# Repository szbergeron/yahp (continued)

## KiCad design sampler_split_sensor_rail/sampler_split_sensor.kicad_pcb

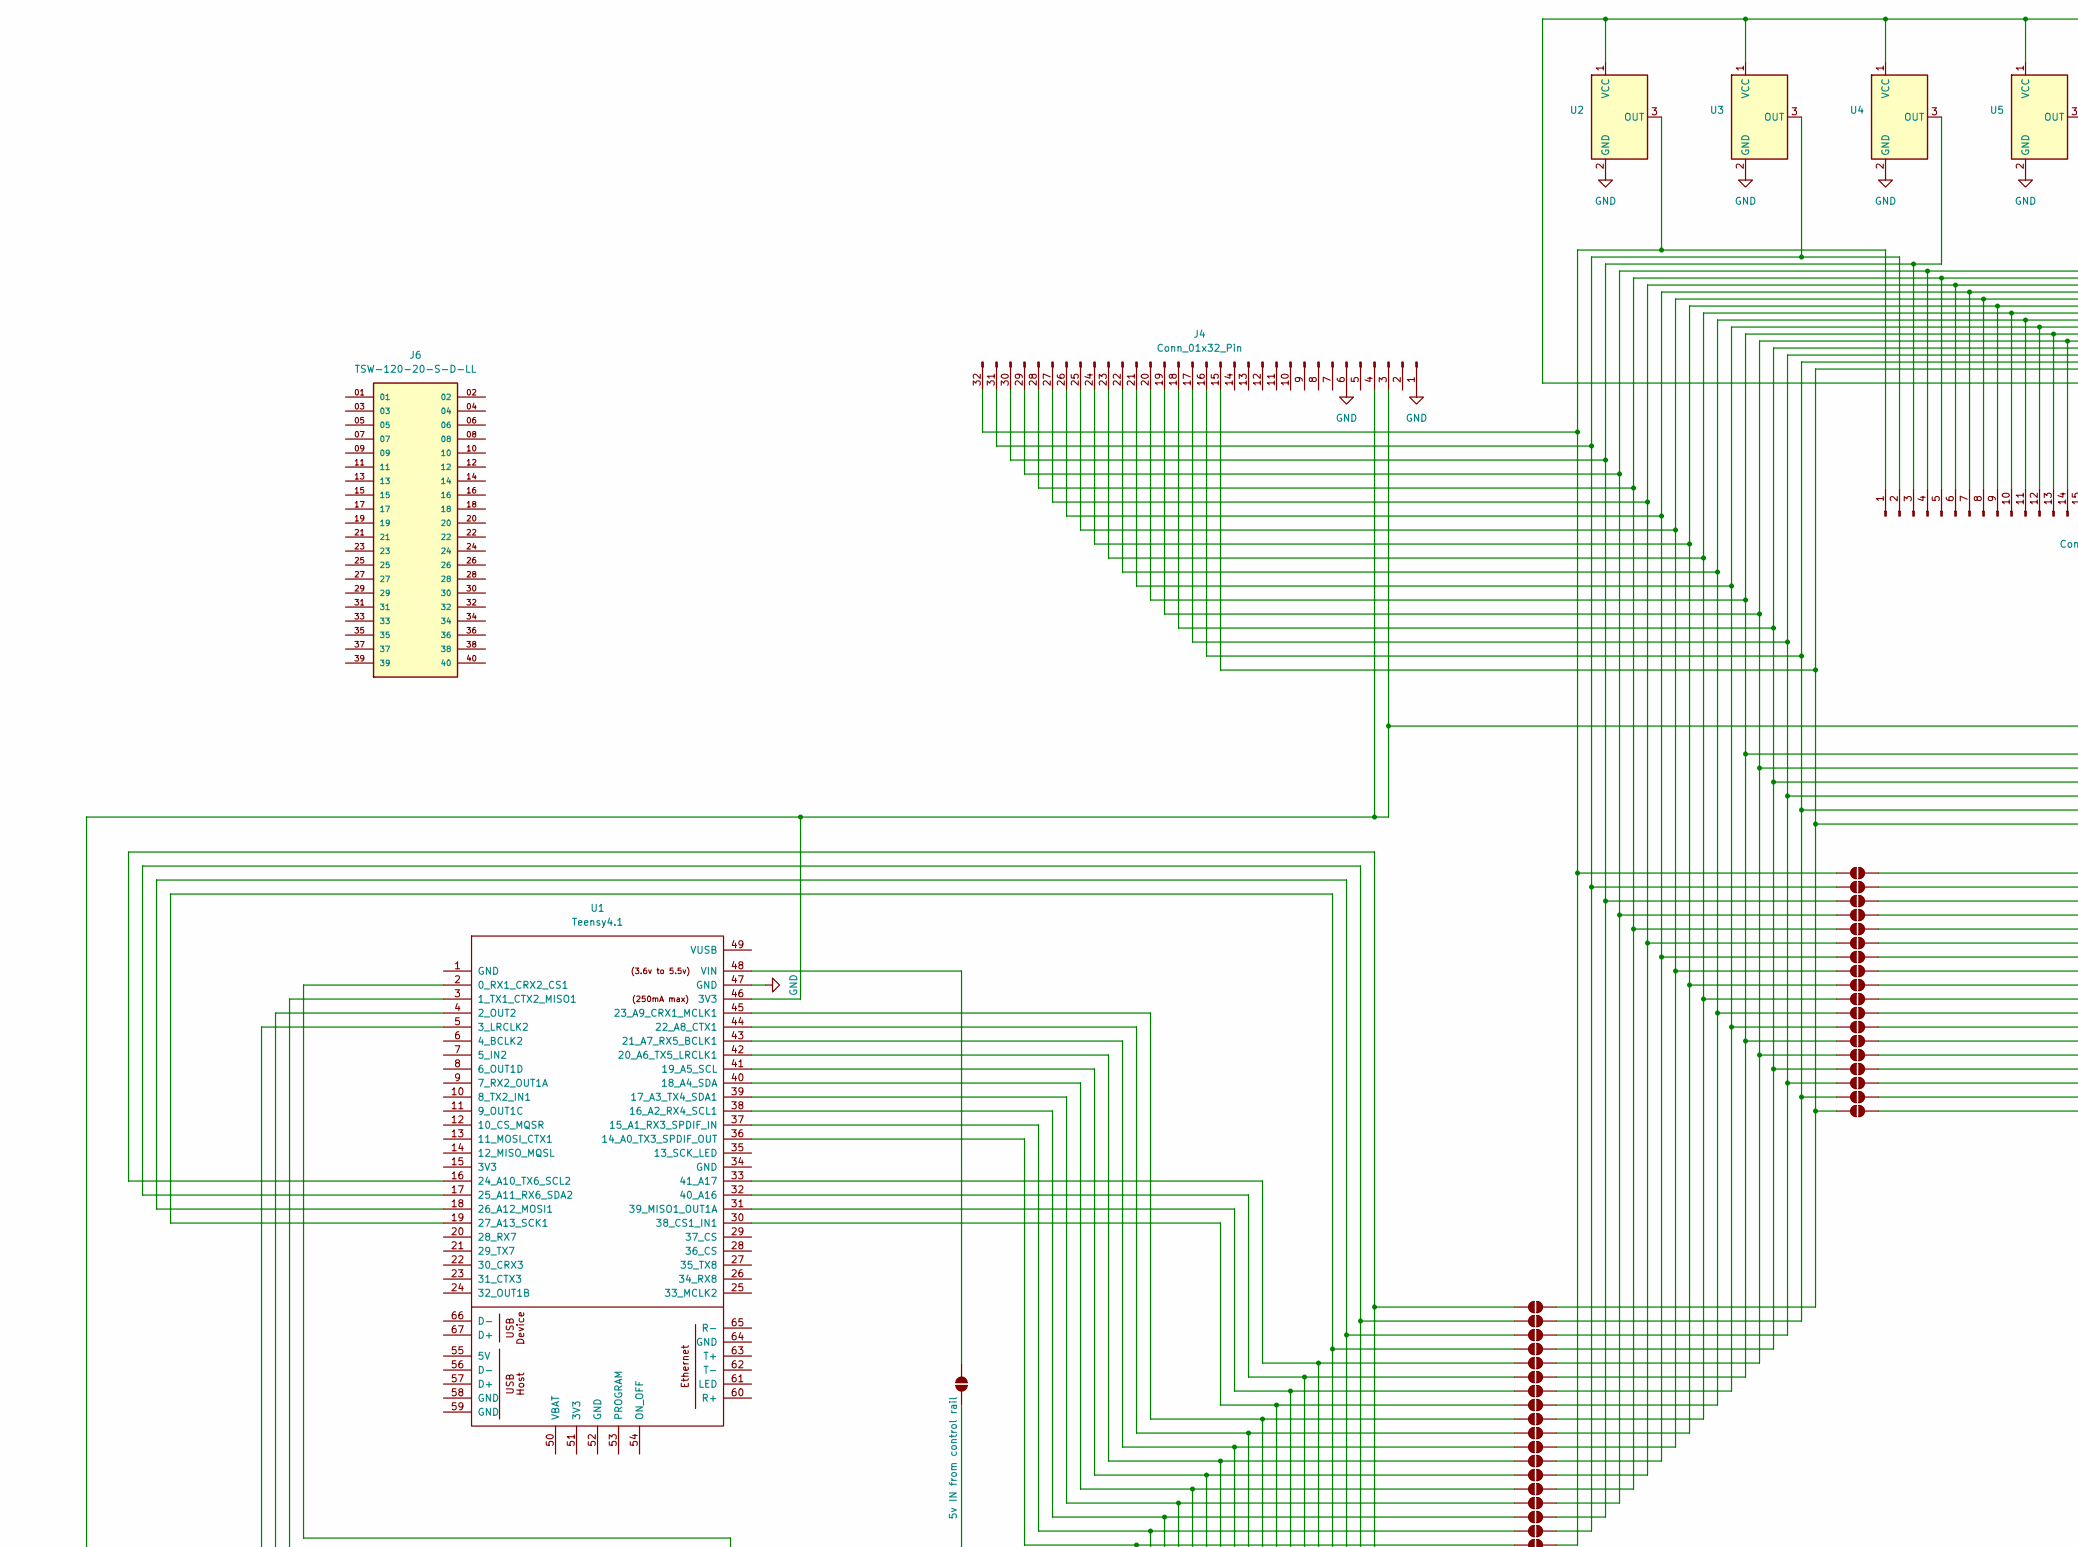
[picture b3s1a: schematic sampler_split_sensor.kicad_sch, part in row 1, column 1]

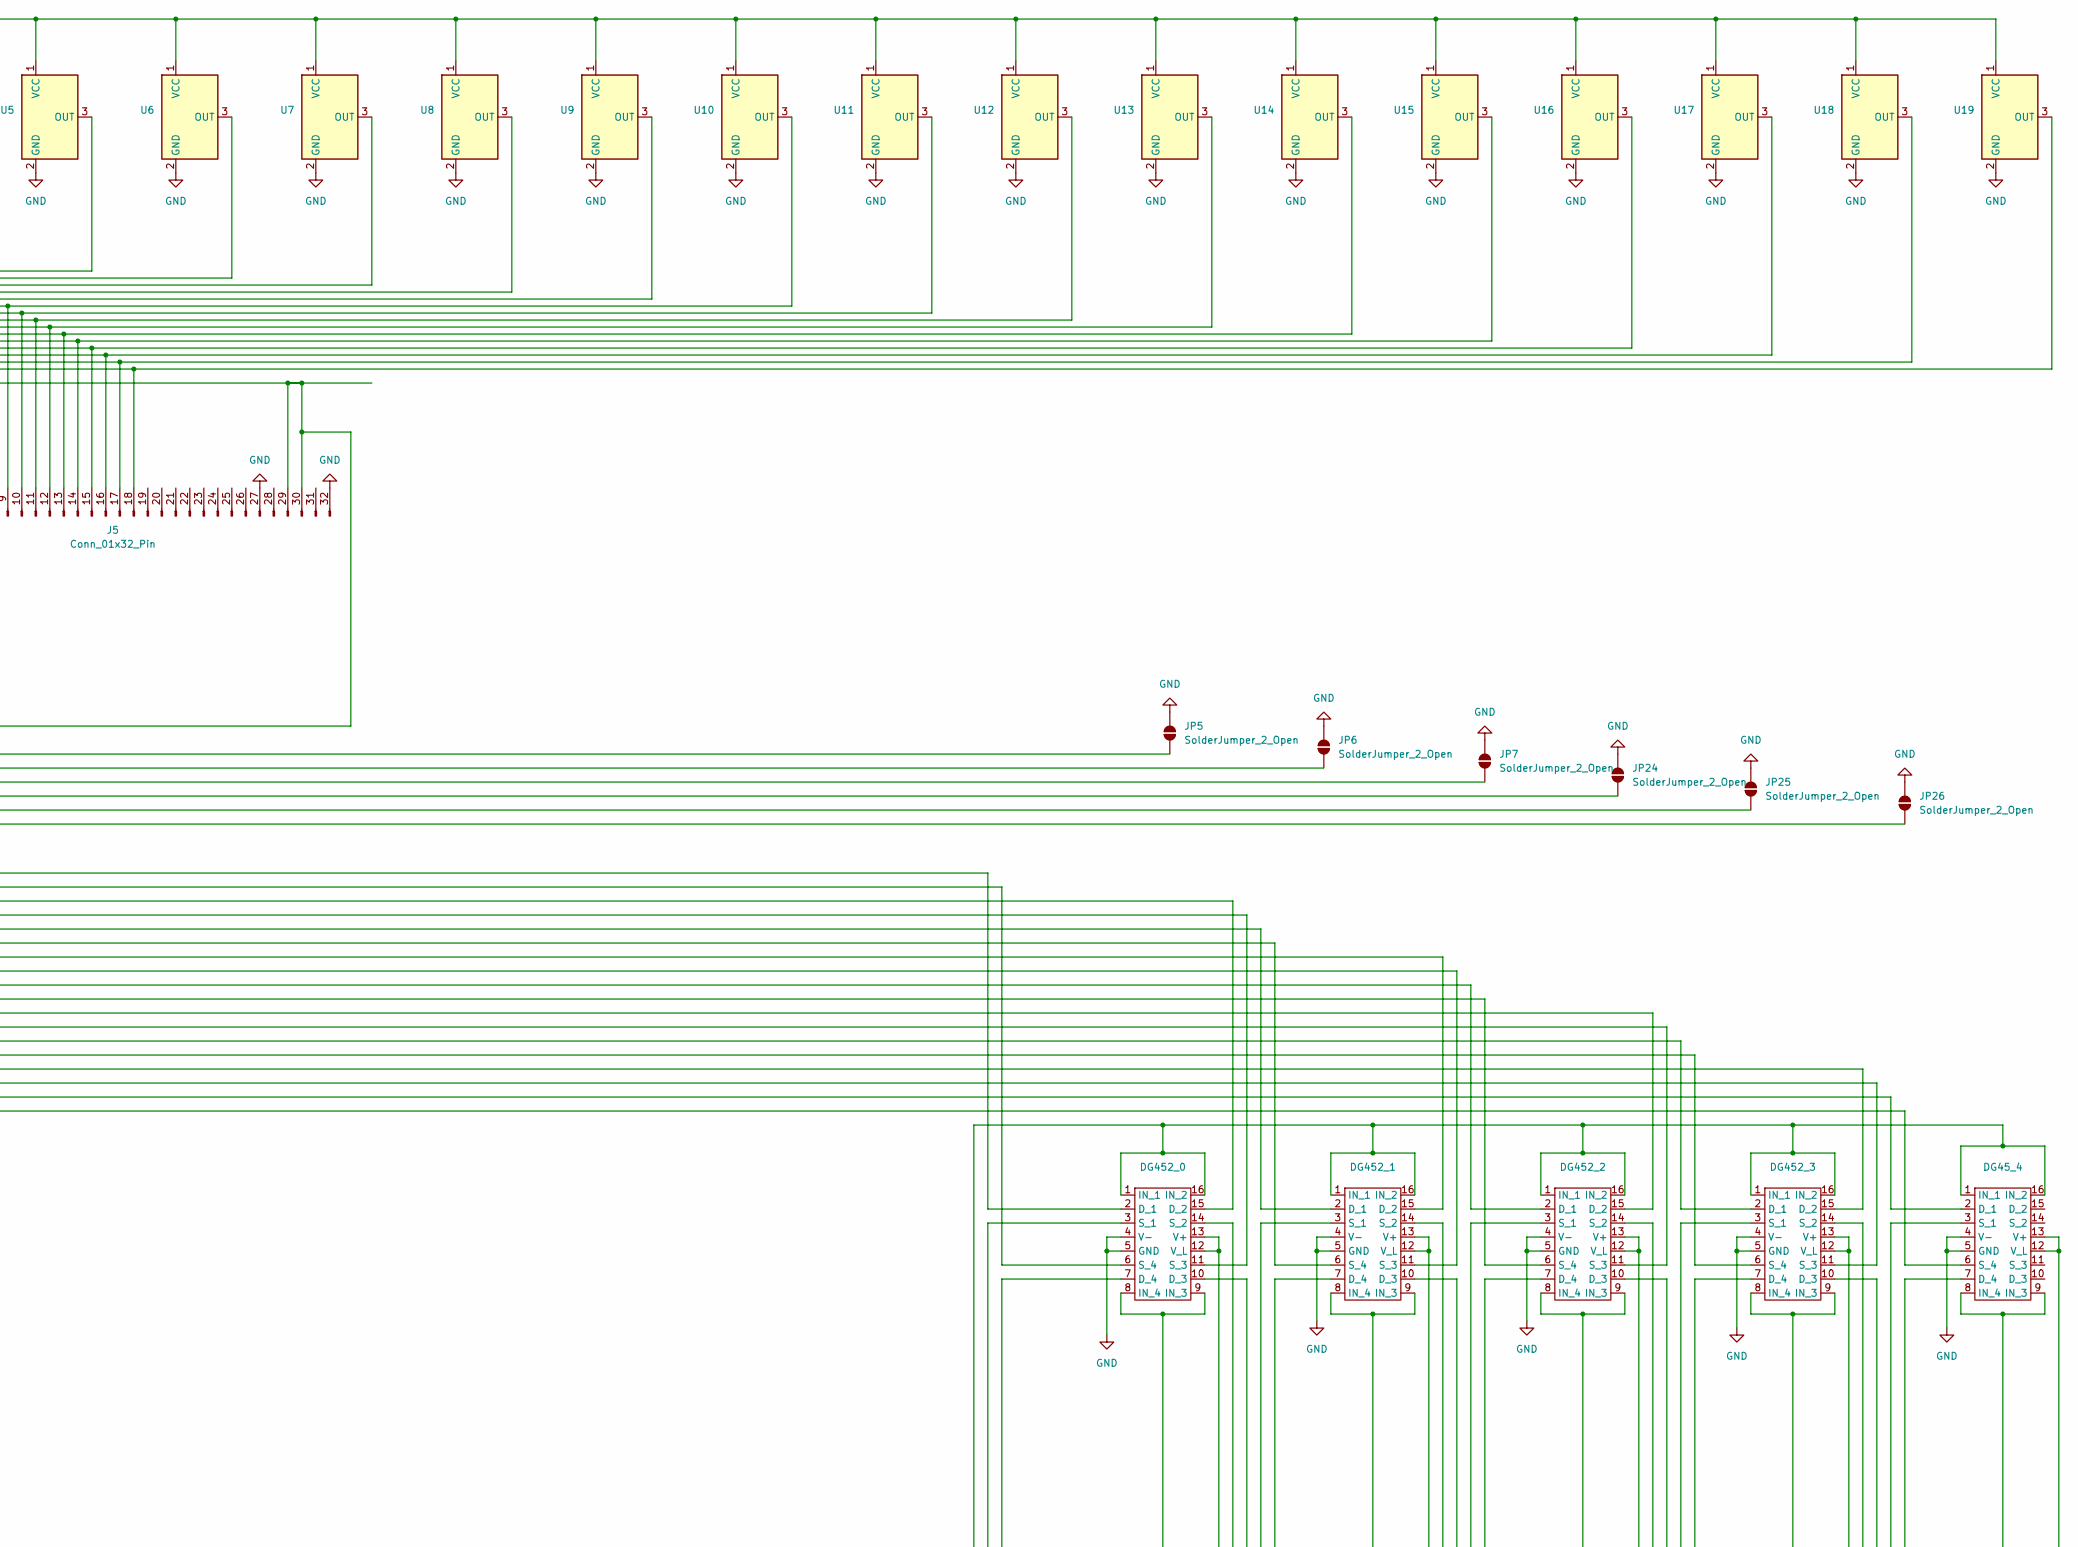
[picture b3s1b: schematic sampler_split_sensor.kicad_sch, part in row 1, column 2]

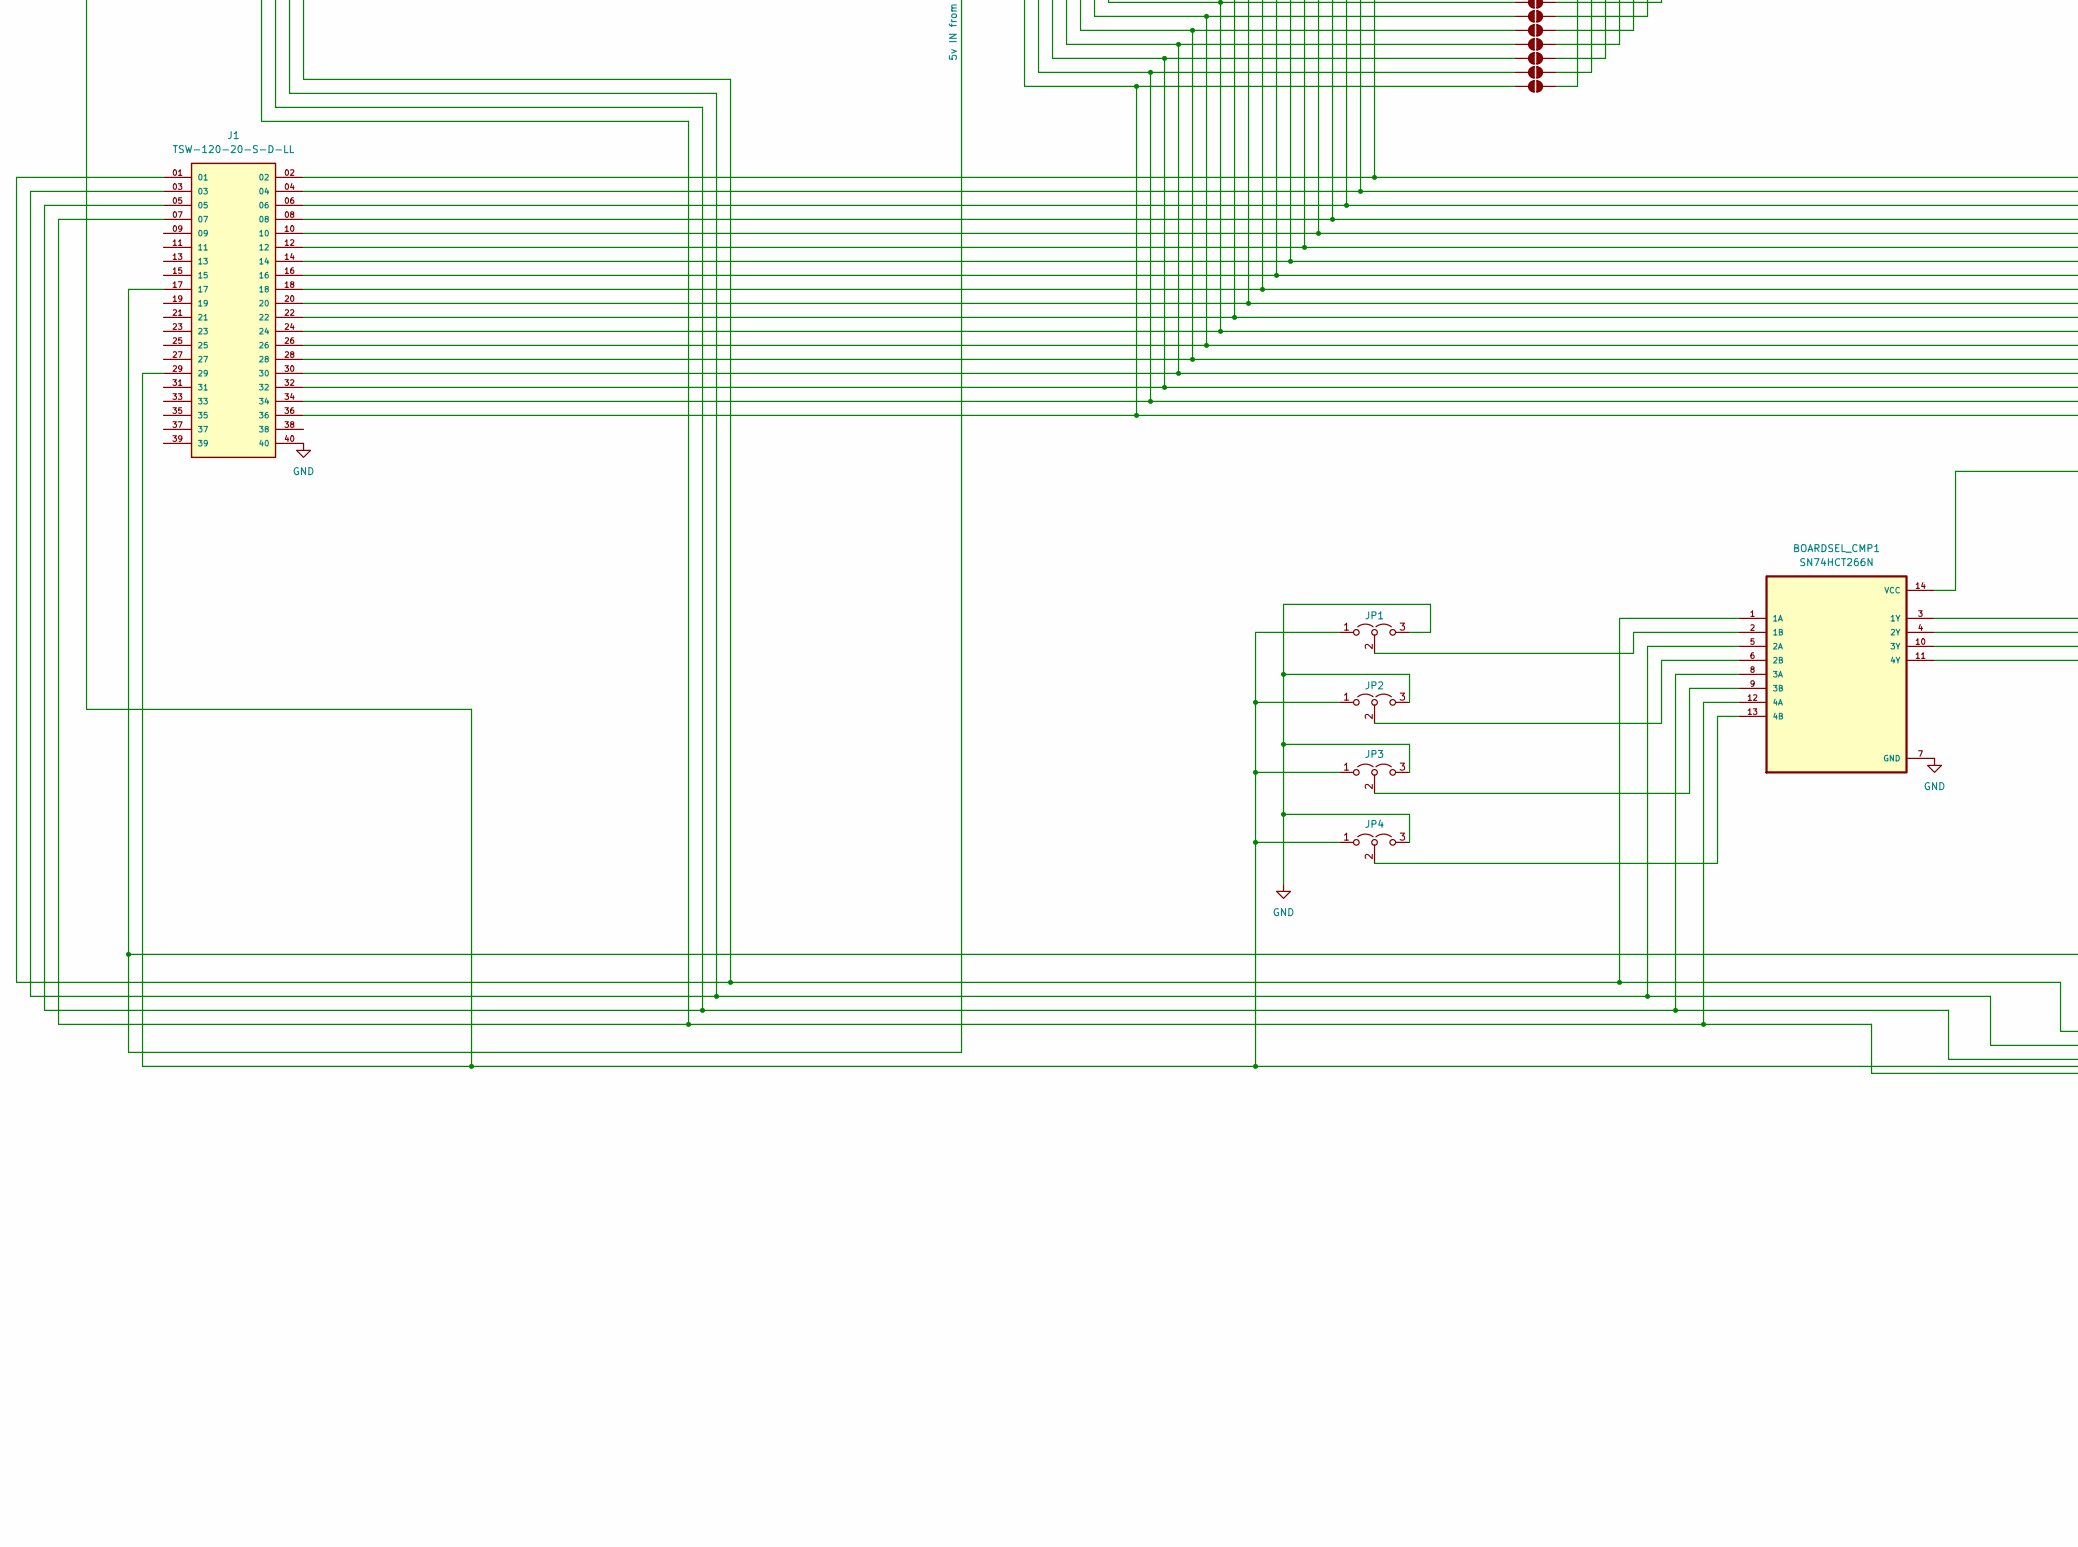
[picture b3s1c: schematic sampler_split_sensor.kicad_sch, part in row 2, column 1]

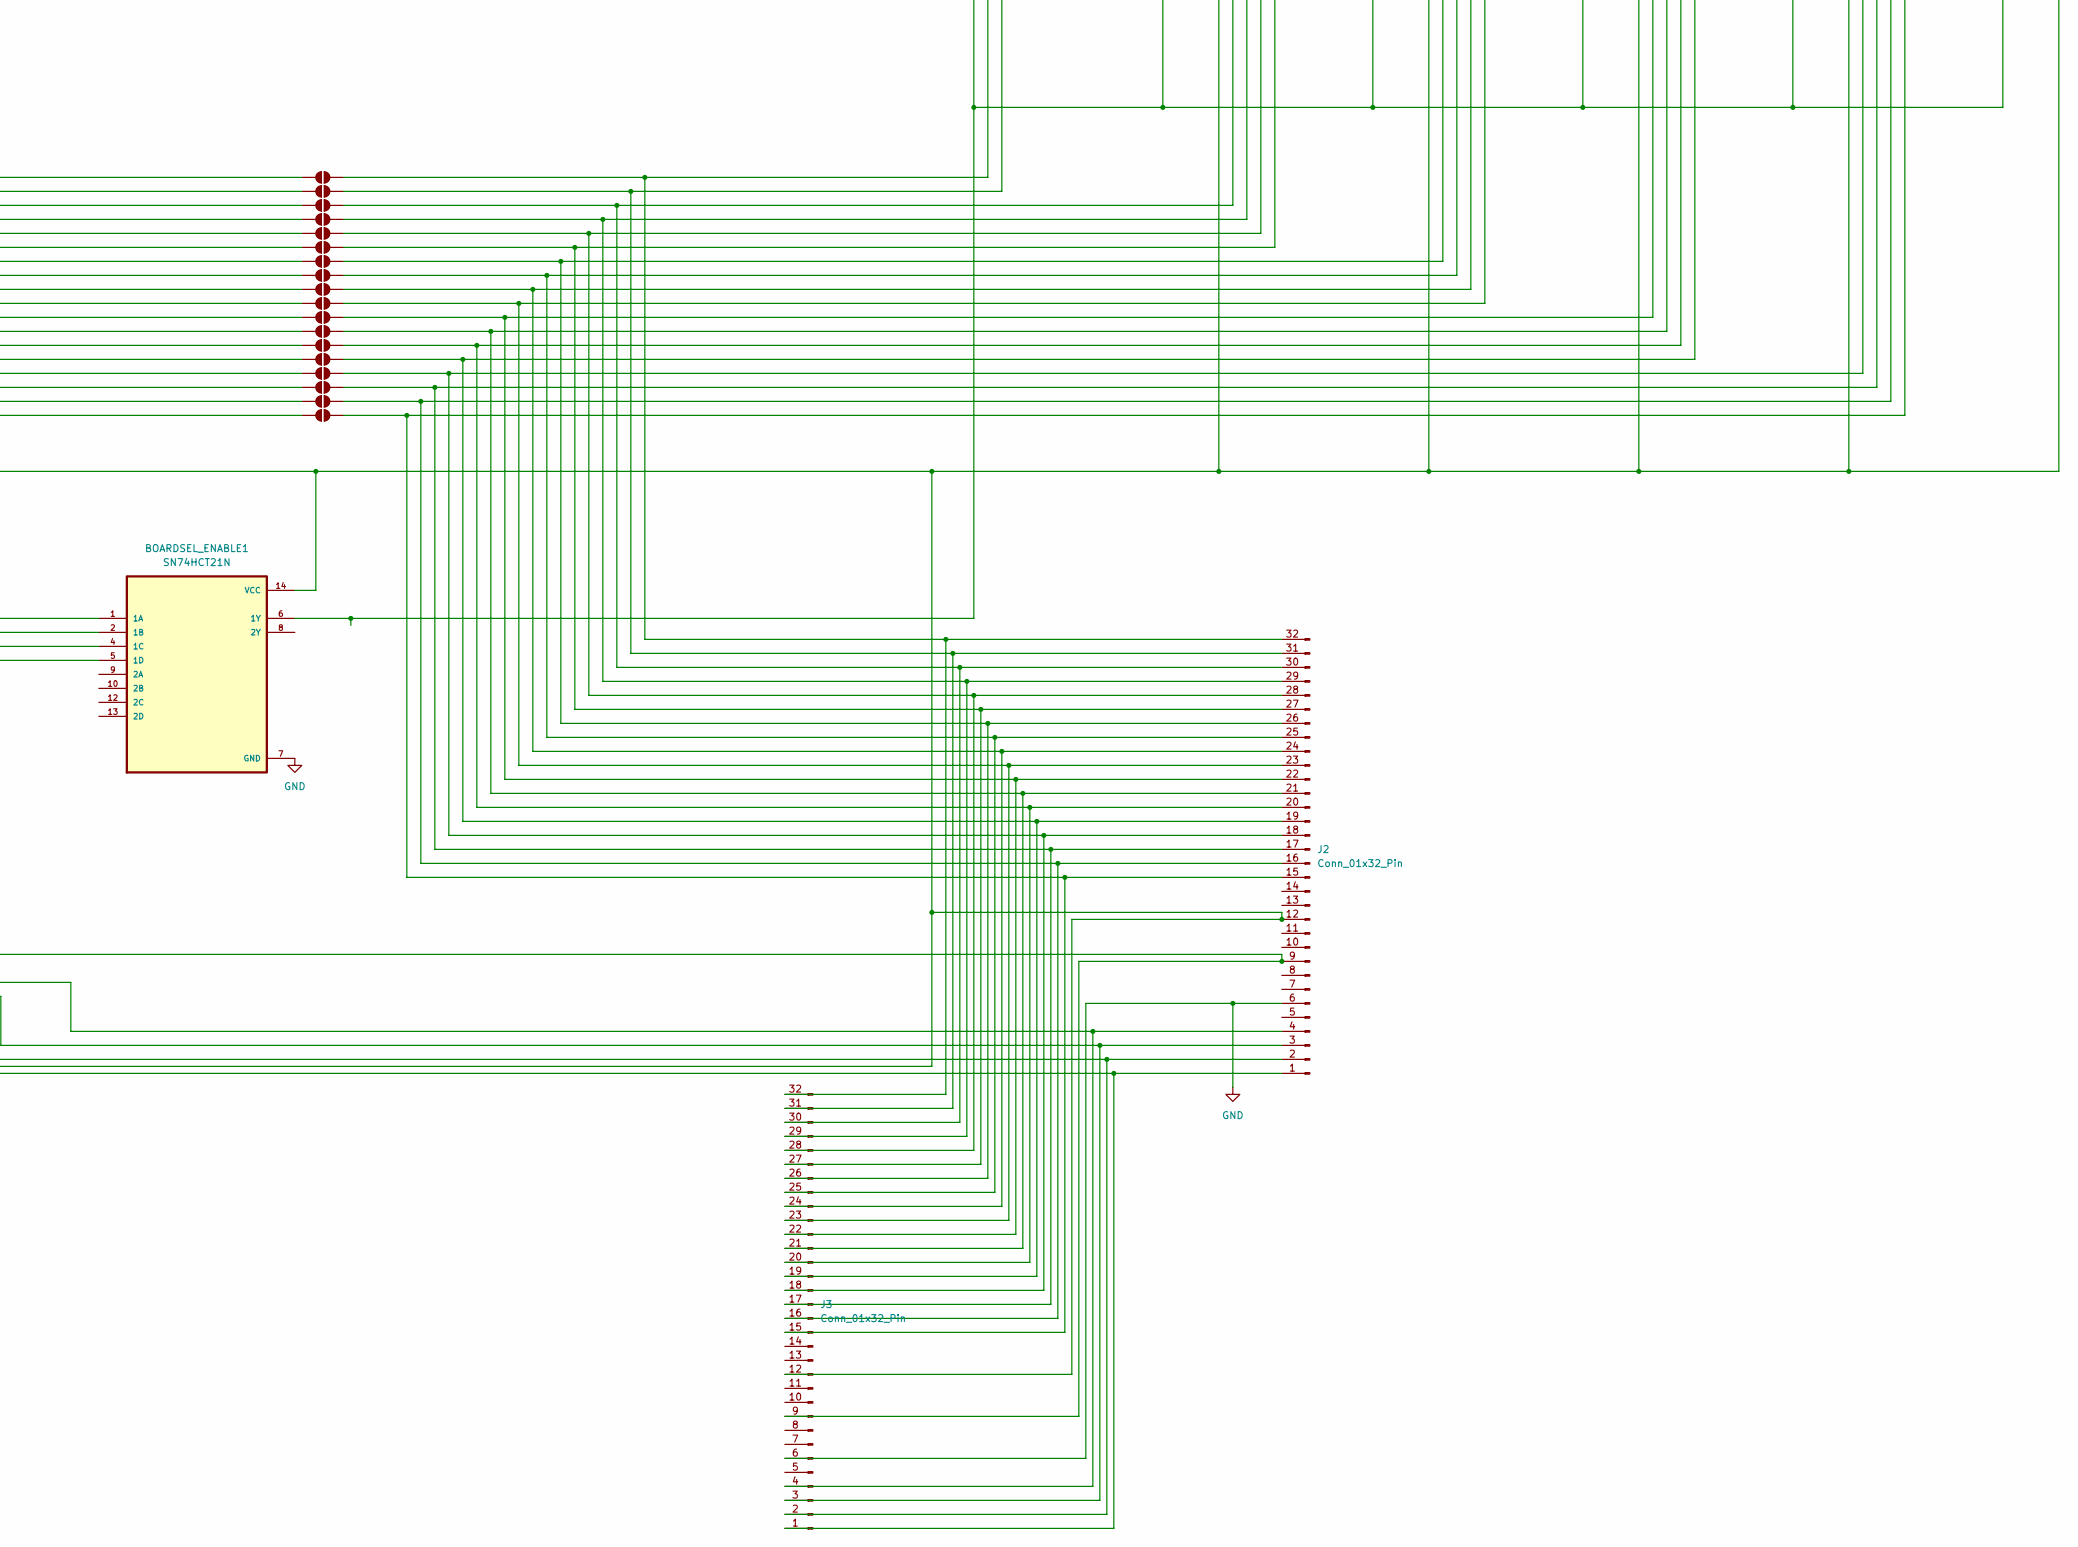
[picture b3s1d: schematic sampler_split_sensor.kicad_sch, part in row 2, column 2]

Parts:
BOARDSEL_CMP1: SN74HCT266N; DIP794W45P254L1969H508Q14
BOARDSEL_ENABLE1: SN74HCT21N; DIP794W45P254L1969H508Q14
DG45_4, DG452_0, DG452_1, DG452_2, DG452_3: SOIC127P600X175-16N
J1, J6: TSW-120-20-S-D-LL; SAMTEC_TSW-120-20-S-D-LL; PARTREV R
J2, J3, J4, J5: Conn_01x32_Pin; Conn_1x32_SMD
JP1, JP2, JP3, JP4: Jumper_3_Open; SolderJumper-3_P2.0mm_Open_TrianglePad1.0x1.5mm
JP5, JP6, JP7, JP8, JP9, JP10, JP11, JP12, JP13, JP14, JP15, JP16, JP17, JP18, JP19, JP20, JP21, JP22, JP24, JP25, JP26, JP45, JP46, JP47, JP48, JP49, JP50, JP51, JP52, JP53, JP54, JP55, JP56, JP57, JP58, JP59, JP60, JP61, JP62, JP63, JP64, JP65: SolderJumper_2_Open; SolderJumper-2_P1.3mm_Open_TrianglePad1.0x1.5mm
JP23: 5v IN from control rail; SolderJumper-2_P1.3mm_Open_TrianglePad1.0x1.5mm
JPE01, JPE02, JPE03, JPE04, JPE05, JPE06, JPE07, JPE08, JPE09, JPE10, JPE11, JPE12, JPE13, JPE14, JPE15, JPE16, JPE17, JPE18: SolderJumper_2_Open; SolderJumper-2_P1.3mm_Open_TrianglePad1.0x1.5mm
U1: Teensy4.1; Teensy41
U2, U3: DRV5055A1xLPGxQ1; TO-92_Inline_Wide
U4, U5: DRV5055A1xLPGxQ1; TO-92_Wide
U6, U7, U8, U9, U10, U11, U12, U13, U14, U15, U16, U17, U18, U19: DRV5055A1xLPGxQ1; TO-92_Inline

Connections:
GND: BOARDSEL_CMP1.7 (GND), BOARDSEL_ENABLE1.7 (GND), DG45_4.4 (V-), DG45_4.5 (GND), DG452_0.4 (V-), DG452_0.5 (GND), DG452_1.4 (V-), DG452_1.5 (GND), DG452_2.4 (V-), DG452_2.5 (GND), DG452_3.4 (V-), DG452_3.5 (GND), J1.40, J2.6, J3.6, J4.1, J4.6, J5.27, J5.32, JP1.3 (B), JP2.3 (B), JP3.3 (B), JP4.3 (B), JP5.1 (A), JP6.1 (A), JP7.1 (A), JP24.1 (A), JP25.1 (A), JP26.1 (A), U1.47 (GND), U2.2 (GND), U3.2 (GND), U4.2 (GND), U5.2 (GND), U6.2 (GND), U7.2 (GND), U8.2 (GND), U9.2 (GND), U10.2 (GND), U11.2 (GND), U12.2 (GND), U13.2 (GND), U14.2 (GND), U15.2 (GND), U16.2 (GND), U17.2 (GND), U18.2 (GND), U19.2 (GND)
unnamed: BOARDSEL_CMP1.1 (1A), J1.01, J2.4, J3.4, U1.2 (0_RX1_CRX2_CS1)
unnamed: BOARDSEL_CMP1.2 (1B), JP1.2 (C)
unnamed: BOARDSEL_CMP1.3 (1Y), BOARDSEL_ENABLE1.1 (1A)
unnamed: BOARDSEL_CMP1.5 (2A), J1.03, J2.3, J3.3, U1.3 (1_TX1_CTX2_MISO1)
unnamed: BOARDSEL_CMP1.6 (2B), JP2.2 (C)
unnamed: BOARDSEL_CMP1.4 (2Y), BOARDSEL_ENABLE1.2 (1B)
unnamed: BOARDSEL_CMP1.8 (3A), J1.05, J2.2, J3.2, U1.4 (2_OUT2)
unnamed: BOARDSEL_CMP1.9 (3B), JP3.2 (C)
unnamed: BOARDSEL_CMP1.10 (3Y), BOARDSEL_ENABLE1.4 (1C)
unnamed: BOARDSEL_CMP1.12 (4A), J1.07, J2.1, J3.1, U1.5 (3_LRCLK2)
unnamed: BOARDSEL_CMP1.13 (4B), JP4.2 (C)
unnamed: BOARDSEL_CMP1.11 (4Y), BOARDSEL_ENABLE1.5 (1D)
unnamed: BOARDSEL_CMP1.14 (VCC), BOARDSEL_ENABLE1.14 (VCC), DG45_4.12 (V_L), DG45_4.13 (V+), DG452_0.12 (V_L), DG452_0.13 (V+), DG452_1.12 (V_L), DG452_1.13 (V+), DG452_2.12 (V_L), DG452_2.13 (V+), DG452_3.12 (V_L), DG452_3.13 (V+), J1.29, J2.12, J3.12, J4.3, J4.4, J5.29, J5.30, JP1.1 (A), JP2.1 (A), JP3.1 (A), JP4.1 (A), U1.46 (3V3), U2.1 (VCC), U3.1 (VCC), U4.1 (VCC), U5.1 (VCC), U6.1 (VCC), U7.1 (VCC), U8.1 (VCC), U9.1 (VCC), U10.1 (VCC), U11.1 (VCC), U12.1 (VCC), U13.1 (VCC), U14.1 (VCC), U15.1 (VCC), U16.1 (VCC), U17.1 (VCC), U18.1 (VCC), U19.1 (VCC)
unnamed: BOARDSEL_ENABLE1.6 (1Y), DG45_4.1 (IN_1), DG45_4.8 (IN_4), DG45_4.9 (IN_3), DG45_4.16 (IN_2), DG452_0.1 (IN_1), DG452_0.8 (IN_4), DG452_0.9 (IN_3), DG452_0.16 (IN_2), DG452_1.1 (IN_1), DG452_1.8 (IN_4), DG452_1.9 (IN_3), DG452_1.16 (IN_2), DG452_2.1 (IN_1), DG452_2.8 (IN_4), DG452_2.9 (IN_3), DG452_2.16 (IN_2), DG452_3.1 (IN_1), DG452_3.8 (IN_4), DG452_3.9 (IN_3), DG452_3.16 (IN_2)
unnamed: DG45_4.2 (D_1), JP64.2 (B)
unnamed: DG45_4.7 (D_4), J2.15, J3.15, JPE18.2 (B)
unnamed: DG45_4.3 (S_1), J2.16, J3.16, JPE17.2 (B)
unnamed: DG45_4.6 (S_4), JP65.2 (B)
unnamed: DG452_0.2 (D_1), JP48.2 (B)
unnamed: DG452_0.15 (D_2), JP50.2 (B)
unnamed: DG452_0.10 (D_3), J2.29, J3.29, JPE04.2 (B)
unnamed: DG452_0.7 (D_4), J2.31, J3.31, JPE02.2 (B)
unnamed: DG452_0.3 (S_1), J2.32, J3.32, JPE01.2 (B)
unnamed: DG452_0.14 (S_2), J2.30, J3.30, JPE03.2 (B)
unnamed: DG452_0.11 (S_3), JP51.2 (B)
unnamed: DG452_0.6 (S_4), JP49.2 (B)
unnamed: DG452_1.2 (D_1), JP52.2 (B)
unnamed: DG452_1.15 (D_2), JP54.2 (B)
unnamed: DG452_1.10 (D_3), J2.25, J3.25, JPE08.2 (B)
unnamed: DG452_1.7 (D_4), J2.27, J3.27, JPE06.2 (B)
unnamed: DG452_1.3 (S_1), J2.28, J3.28, JPE05.2 (B)
unnamed: DG452_1.14 (S_2), J2.26, J3.26, JPE07.2 (B)
unnamed: DG452_1.11 (S_3), JP55.2 (B)
unnamed: DG452_1.6 (S_4), JP53.2 (B)
unnamed: DG452_2.2 (D_1), JP56.2 (B)
unnamed: DG452_2.15 (D_2), JP58.2 (B)
unnamed: DG452_2.10 (D_3), J2.21, J3.21, JPE12.2 (B)
unnamed: DG452_2.7 (D_4), J2.23, J3.23, JPE10.2 (B)
unnamed: DG452_2.3 (S_1), J2.24, J3.24, JPE09.2 (B)
unnamed: DG452_2.14 (S_2), J2.22, J3.22, JPE11.2 (B)
unnamed: DG452_2.11 (S_3), JP59.2 (B)
unnamed: DG452_2.6 (S_4), JP57.2 (B)
unnamed: DG452_3.2 (D_1), JP60.2 (B)
unnamed: DG452_3.15 (D_2), JP62.2 (B)
unnamed: DG452_3.10 (D_3), J2.17, J3.17, JPE16.2 (B)
unnamed: DG452_3.7 (D_4), J2.19, J3.19, JPE14.2 (B)
unnamed: DG452_3.3 (S_1), J2.20, J3.20, JPE13.2 (B)
unnamed: DG452_3.14 (S_2), J2.18, J3.18, JPE15.2 (B)
unnamed: DG452_3.11 (S_3), JP63.2 (B)
unnamed: DG452_3.6 (S_4), JP61.2 (B)
unnamed: J1.17, J2.9, J3.9, JP23.1 (A)
unnamed: J4.15, J5.18, JP8.2 (B), JP26.2 (B), JP65.1 (A), U19.3 (OUT)
unnamed: J4.16, J5.17, JP9.2 (B), JP25.2 (B), JP64.1 (A), U18.3 (OUT)
unnamed: J4.17, J5.16, JP10.2 (B), JP24.2 (B), JP63.1 (A), U17.3 (OUT)
unnamed: J4.18, J5.15, JP7.2 (B), JP11.2 (B), JP62.1 (A), U16.3 (OUT)
unnamed: J4.19, J5.14, JP6.2 (B), JP12.2 (B), JP61.1 (A), U15.3 (OUT)
unnamed: J4.20, J5.13, JP5.2 (B), JP13.2 (B), JP60.1 (A), U14.3 (OUT)
unnamed: J4.21, J5.12, JP14.2 (B), JP59.1 (A), U13.3 (OUT)
unnamed: J4.22, J5.11, JP15.2 (B), JP58.1 (A), U12.3 (OUT)
unnamed: J4.23, J5.10, JP16.2 (B), JP57.1 (A), U11.3 (OUT)
unnamed: J4.24, J5.9, JP17.2 (B), JP56.1 (A), U10.3 (OUT)
unnamed: J4.25, J5.8, JP18.2 (B), JP55.1 (A), U9.3 (OUT)
unnamed: J4.26, J5.7, JP19.2 (B), JP54.1 (A), U8.3 (OUT)
unnamed: J4.27, J5.6, JP20.2 (B), JP53.1 (A), U7.3 (OUT)
unnamed: J4.28, J5.5, JP21.2 (B), JP52.1 (A), U6.3 (OUT)
unnamed: J4.29, J5.4, JP22.2 (B), JP51.1 (A), U5.3 (OUT)
unnamed: J4.30, J5.3, JP45.2 (B), JP50.1 (A), U4.3 (OUT)
unnamed: J4.31, J5.2, JP46.2 (B), JP49.1 (A), U3.3 (OUT)
unnamed: J4.32, J5.1, JP47.2 (B), JP48.1 (A), U2.3 (OUT)
unnamed: J1.02, JP8.1 (A), JPE01.1 (A), U1.16 (24_A10_TX6_SCL2)
unnamed: J1.04, JP9.1 (A), JPE02.1 (A), U1.17 (25_A11_RX6_SDA2)
unnamed: J1.06, JP10.1 (A), JPE03.1 (A), U1.18 (26_A12_MOSI1)
unnamed: J1.08, JP11.1 (A), JPE04.1 (A), U1.19 (27_A13_SCK1)
unnamed: J1.10, JP12.1 (A), JPE05.1 (A), U1.33 (41_A17)
unnamed: J1.12, JP13.1 (A), JPE06.1 (A), U1.32 (40_A16)
unnamed: J1.14, JP14.1 (A), JPE07.1 (A), U1.31 (39_MISO1_OUT1A)
unnamed: J1.16, JP15.1 (A), JPE08.1 (A), U1.30 (38_CS1_IN1)
unnamed: J1.18, JP16.1 (A), JPE09.1 (A), U1.45 (23_A9_CRX1_MCLK1)
unnamed: J1.20, JP17.1 (A), JPE10.1 (A), U1.44 (22_A8_CTX1)
unnamed: J1.22, JP18.1 (A), JPE11.1 (A), U1.43 (21_A7_RX5_BCLK1)
unnamed: J1.24, JP19.1 (A), JPE12.1 (A), U1.42 (20_A6_TX5_LRCLK1)
unnamed: J1.26, JP20.1 (A), JPE13.1 (A), U1.41 (19_A5_SCL)
unnamed: J1.28, JP21.1 (A), JPE14.1 (A), U1.40 (18_A4_SDA)
unnamed: J1.30, JP22.1 (A), JPE15.1 (A), U1.39 (17_A3_TX4_SDA1)
unnamed: JP23.2 (B), U1.48 (VIN)
unnamed: J1.32, JP45.1 (A), JPE16.1 (A), U1.38 (16_A2_RX4_SCL1)
unnamed: J1.34, JP46.1 (A), JPE17.1 (A), U1.37 (15_A1_RX3_SPDIF_IN)
unnamed: J1.36, JP47.1 (A), JPE18.1 (A), U1.36 (14_A0_TX3_SPDIF_OUT)

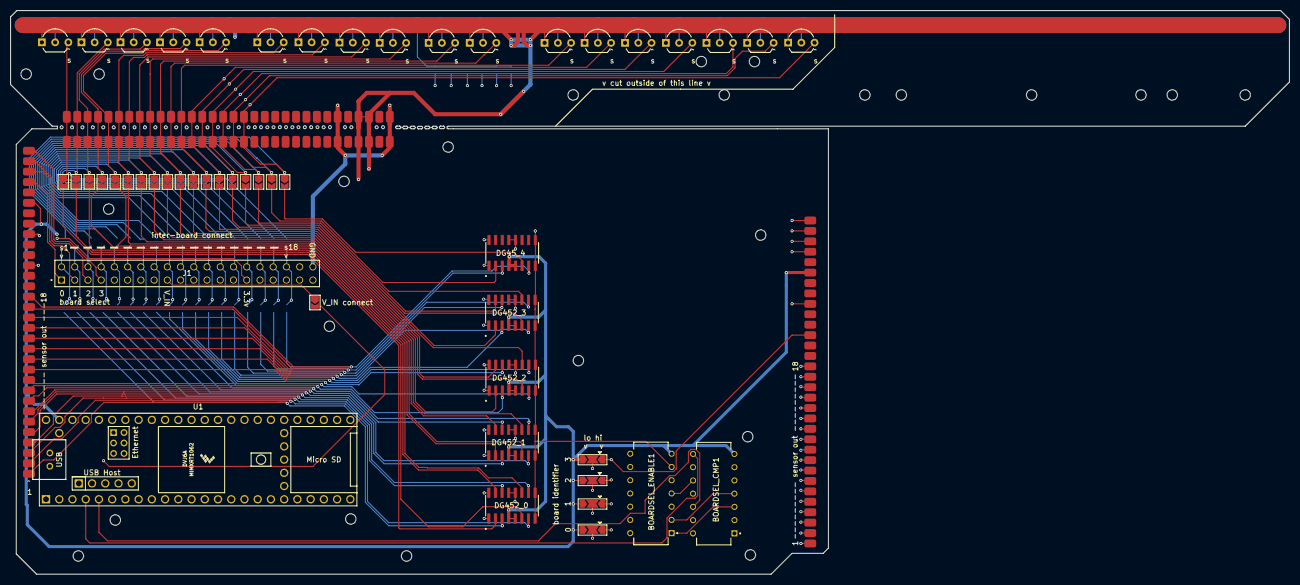
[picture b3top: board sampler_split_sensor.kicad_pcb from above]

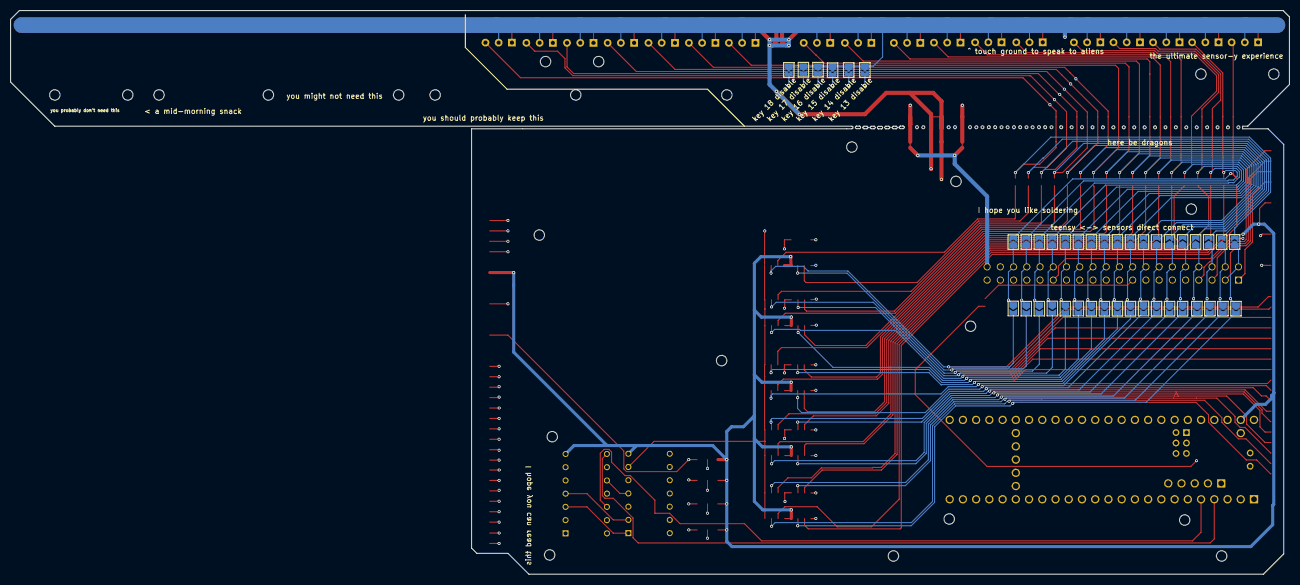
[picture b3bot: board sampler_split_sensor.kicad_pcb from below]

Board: 4 copper layers, 245.5 x 108.2 mm, 96 parts (42 on the bottom side), 89 nets.

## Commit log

2024-06-07 Initial PoC
2024-06-07 Midi controller moment
2024-06-13 Calibration tweaks
2024-06-18 add schematics, some updates to deal with key attention
2024-06-19 cleanup
2024-06-20 design PCB
2024-06-21 add split sensor board for breakaway
2024-07-06 Boards v3
2024-07-06 readme discussion
2024-07-09 fixes
2024-07-11 boards
2024-07-19 iter
2024-07-20 I'm so f*cking tired rn this might as well be drunk code
2024-07-22 mid-rewrite and the weekend's over
2024-07-22 idk adc stuff or something
2024-07-23 big changes
2024-07-24 stuff
2024-07-24 sampler
2024-07-25 something is horribly broken?
2024-07-25 fixed it \:)
2024-07-25 this makes no sense
2024-07-25 fixed???
2024-07-25 absolutely weird fuckery
2024-07-25 so fucking dumb
2024-07-25 idk wtf is wrong with this
2024-07-27 work on shit
2024-07-29 start doing piecewise linear
2024-07-29 a whole lot of calibration stuff ig
2024-07-29 shit
2024-07-29 forgot
2024-07-29 fix things
2024-07-30 yeet
2024-07-30 working toward modular sd stuff
2024-07-30 ignore compile commands
2024-07-30 Fix gitignore
2024-07-30 <creative commit message #18794>
2024-07-30 push stuff from this morning
2024-07-31 akshita wants to use netflix
2024-07-31 wooooooooooooooooooo
2024-08-01 why don't multiple board work???
2024-08-02 im a feckin jenius amen
2024-08-13 Mostly works for calibration,
    but going to save off and redo a bunch of the calibration flow
    to induce fewer measurement errors and allow better flexibility in the
    face of "screwing it up" on a fastcal run
2024-08-14 push for dt
2024-08-27 start work on perf opt
2024-09-01 stability fixes
2025-01-20 start on new arch: rust on pi, flatbuffers for transit, teensy as smart adc, and dioxus for ui
